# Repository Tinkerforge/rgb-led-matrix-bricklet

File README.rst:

RGB LED Matrix Bricklet
=======================

This repository contains the firmware source code and the hardware design
files. The documentation generator configs can be found at
https://github.com/Tinkerforge/generators

Repository Content
------------------

software/:
 * examples/: Examples for all supported languages
 * build/: Compiled files
 * src/: Source code of firmware
 * Makefile: Makefile to build project

hardware/:
 * Contains KiCad project files and additionally schematics as PDF

datasheets/:
 * Contains datasheets for sensors and complex ICs that are used

Hardware
--------

The hardware is designed with the open source EDA Suite KiCad
(http://www.kicad.org). Before you are able to open the files,
you have to install the Tinkerforge kicad-libraries
(https://github.com/Tinkerforge/kicad-libraries). You can either clone
them directly in hardware/ or clone them in a separate folder and
symlink them into hardware/
(ln -s kicad_path/kicad-libraries project_path/hardware). After that you
can open the .pro file in hardware/ with KiCad and from there view and
modify the schematics and the PCB layout.

Software
--------

If you want to do your own Brick/Bricklet firmware development we highly
recommend that you use our build environment setup script and read the
tutorial (https://www.tinkerforge.com/en/doc/Tutorials/Tutorial_Build_Environment/Tutorial.html).

To compile the C code we recommend you to install the newest GNU Arm Embedded
Toolchain (https://launchpad.net/gcc-arm-embedded/+download).
You also need to install bricklib2 (https://github.com/Tinkerforge/bricklib2).

You can either clone it directly in software/src/ or clone it in a
separate folder and symlink it into software/src/
(ln -s bricklib_path/bricklib2 project_path/software/src/). Finally make sure to
have CMake installed (http://www.cmake.org/cmake/resources/software.html).

After that you can build the firmware by invoking make in software/.
The firmware (.zbin) can then be found in software/build/ and uploaded
with brickv (click button "Flashing" on start screen).

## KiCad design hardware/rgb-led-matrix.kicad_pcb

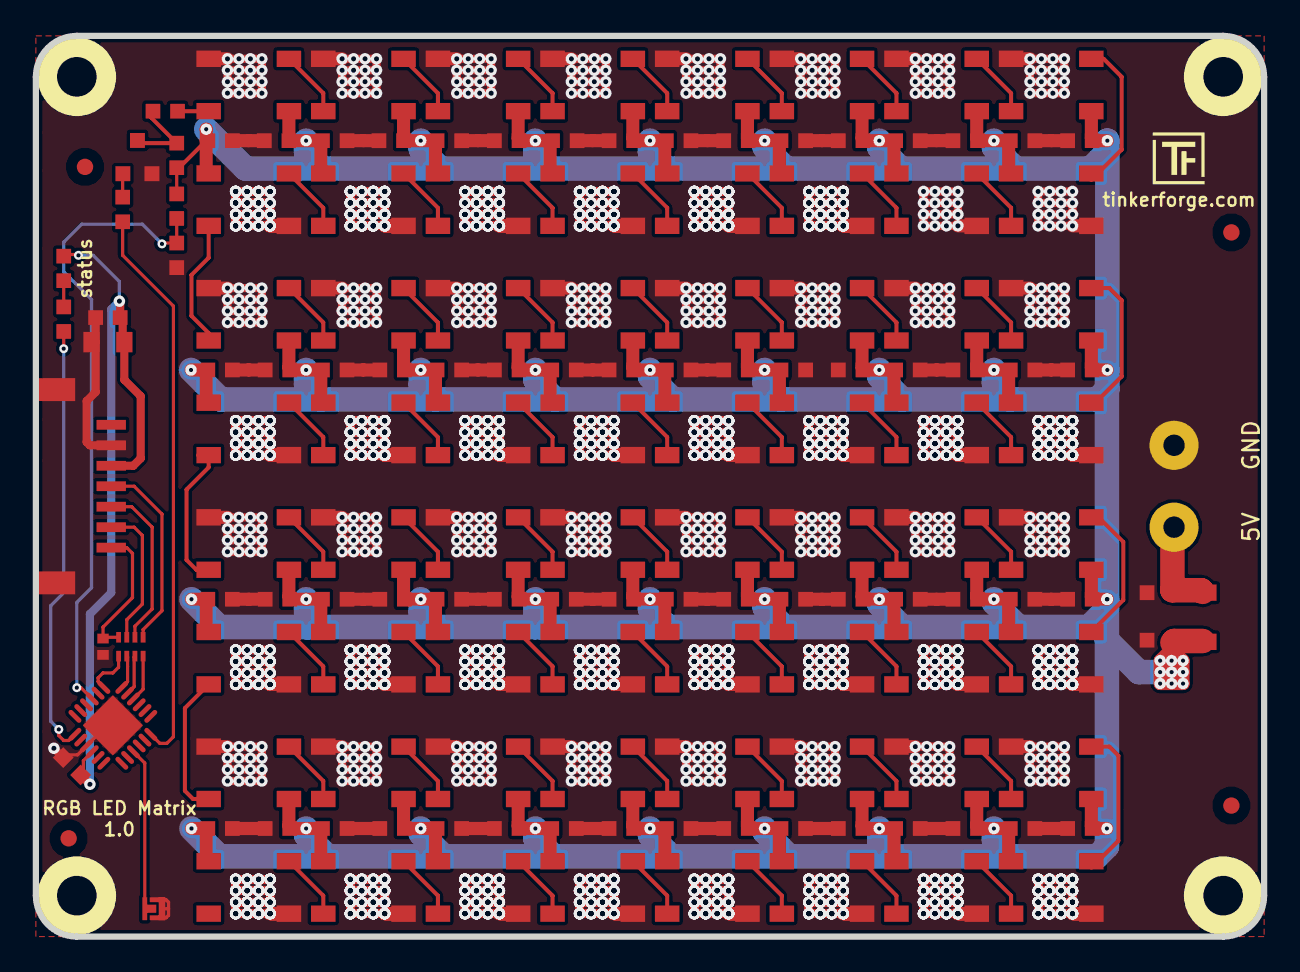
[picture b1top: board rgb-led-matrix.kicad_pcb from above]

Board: 2 copper layers, 75.0 x 55.0 mm, 157 parts (0 on the bottom side), 82 nets.

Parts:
C1, C6, C7, C8, C9, C10, C11, C12, C13, C14, C15, C16, C17, C18, C19, C20, C21, C22, C23, C24, C25, C26, C27, C28, C29, C30, C31, C32, C33, C34, C35, C36, C37, C38, C39, C40, C41, C42, C43, C44, C45, C46, C47, C48, C49, C50, C51, C52, C53, C54, C55, C56, C57, C58, C59, C60, C61, C62, C63, C64, C65, C66, C67, C68, C69: 100nF; C0603F
C2, C4, C5: 1uF; C0603F
C3: 10uF; C0805
C70: 220pF; C0402F
D1: LED blue; D0603F
FB2: FB 6A; R1206
Fiducial_Mark: VAL**; Fiducial_Mark
Fiducial_Mark#2, Fiducial_Mark#3, Fiducial_Mark#4: VAL**; Fiducial_Mark
J1: AKL_5_2
LED1, LED2, LED3, LED4, LED5, LED6, LED7, LED8, LED9, LED10, LED11, LED12, LED13, LED14, LED15, LED16, LED17, LED18, LED19, LED20, LED21, LED22, LED23, LED24, LED25, LED26, LED27, LED28, LED29, LED30, LED31, LED32, LED33, LED34, LED35, LED36, LED37, LED38, LED39, LED40, LED41, LED42, LED43, LED44, LED45, LED46, LED47, LED48, LED49, LED50, LED51, LED52, LED53, LED54, LED55, LED56, LED57, LED58, LED59, LED60, LED61, LED62, LED63, LED64: WS2812B_LED
P1: CONN_01X02; SolderJumper
P2: CON-SENSOR; CON-SENSOR2
Q1: 2N7002P; SOT23GDS
R1, R2, R5, R6: 1k; R0603F
R3: 100; R0603F
R4: 330; R0603F
RP1: 82; 4X0402
U1: XMC1100-16; QFN24-4x4mm-0.5mm
U2, U3, U4, U5: DRILL; DRILL_NP
VAL: CE_5mm

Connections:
3V3: C1.2, C2.2, C3.2, D1.1, P2.3, U1.10
GND: C1.1, C2.1, C3.1, C4.1, C5.1, C6.2, C7.2, C8.2, C9.2, C10.2, C11.2, C12.2, C13.2, C14.2, C15.2, C16.2, C17.2, C18.2, C19.2, C20.2, C21.2, C22.2, C23.2, C24.2, C25.2, C26.2, C27.2, C28.2, C29.2, C30.2, C31.2, C32.2, C33.2, C34.2, C35.2, C36.2, C37.2, C38.2, C39.2, C40.2, C41.2, C42.2, C43.2, C44.2, C45.2, C46.2, C47.2, C48.2, C49.2, C50.2, C51.2, C52.2, C53.2, C54.2, C55.2, C56.2, C57.2, C58.2, C59.2, C60.2, C61.2, C62.2, C63.2, C64.2, C65.2, C66.2, C67.2, C68.2, C69.2, C70.1, J1.1, LED1.3, LED2.3, LED3.3, LED4.3, LED5.3, LED6.3, LED7.3, LED8.3, LED9.3, LED10.3, LED11.3, LED12.3, LED13.3, LED14.3, LED15.3, LED16.3, LED17.3, LED18.3, LED19.3, LED20.3, LED21.3, LED22.3, LED23.3, LED24.3, LED25.3, LED26.3, LED27.3, LED28.3, LED29.3, LED30.3, LED31.3, LED32.3, LED33.3, LED34.3, LED35.3, LED36.3, LED37.3, LED38.3, LED39.3, LED40.3, LED41.3, LED42.3, LED43.3, LED44.3, LED45.3, LED46.3, LED47.3, LED48.3, LED49.3, LED50.3, LED51.3, LED52.3, LED53.3, LED54.3, LED55.3, LED56.3, LED57.3, LED58.3, LED59.3, LED60.3, LED61.3, LED62.3, LED63.3, LED64.3, P1.1, P2.2, P2.EP, Q1.S, R6.2, U1.9, U1.EXP
unnamed: C5.2, FB2.1, J1.2
unnamed: C70.2, P2.7, RP1.4
unnamed: D1.2, R1.1
unnamed: LED1.2, LED2.4
unnamed: LED1.4, R4.1
unnamed: LED2.2, LED3.4
unnamed: LED3.2, LED4.4
unnamed: LED4.2, LED5.4
unnamed: LED5.2, LED6.4
unnamed: LED6.2, LED7.4
unnamed: LED7.2, LED8.4
unnamed: LED8.2, LED9.4
unnamed: LED10.2, LED11.4
unnamed: LED9.2, LED10.4
unnamed: LED11.2, LED12.4
unnamed: LED12.2, LED13.4
unnamed: LED13.2, LED14.4
unnamed: LED14.2, LED15.4
unnamed: LED15.2, LED16.4
unnamed: LED16.2, LED17.4
unnamed: LED17.2, LED18.4
unnamed: LED18.2, LED19.4
unnamed: LED19.2, LED20.4
unnamed: LED20.2, LED21.4
unnamed: LED21.2, LED22.4
unnamed: LED22.2, LED23.4
unnamed: LED23.2, LED24.4
unnamed: LED24.2, LED25.4
unnamed: LED25.2, LED26.4
unnamed: LED26.2, LED27.4
unnamed: LED27.2, LED28.4
unnamed: LED28.2, LED29.4
unnamed: LED29.2, LED30.4
unnamed: LED30.2, LED31.4
unnamed: LED31.2, LED32.4
unnamed: LED32.2, LED33.4
unnamed: LED33.2, LED34.4
unnamed: LED34.2, LED35.4
unnamed: LED35.2, LED36.4
unnamed: LED36.2, LED37.4
unnamed: LED37.2, LED38.4
unnamed: LED38.2, LED39.4
unnamed: LED39.2, LED40.4
unnamed: LED40.2, LED41.4
unnamed: LED41.2, LED42.4
unnamed: LED42.2, LED43.4
unnamed: LED43.2, LED44.4
unnamed: LED44.2, LED45.4
unnamed: LED45.2, LED46.4
unnamed: LED46.2, LED47.4
unnamed: LED47.2, LED48.4
unnamed: LED48.2, LED49.4
unnamed: LED49.2, LED50.4
unnamed: LED50.2, LED51.4
unnamed: LED51.2, LED52.4
unnamed: LED52.2, LED53.4
unnamed: LED53.2, LED54.4
unnamed: LED54.2, LED55.4
unnamed: LED55.2, LED56.4
unnamed: LED56.2, LED57.4
unnamed: LED57.2, LED58.4
unnamed: LED58.2, LED59.4
unnamed: LED59.2, LED60.4
unnamed: LED60.2, LED61.4
unnamed: LED61.2, LED62.4
unnamed: LED62.2, LED63.4
unnamed: LED63.2, LED64.4
unnamed: P1.2, U1.15
unnamed: P2.4, RP1.1
unnamed: P2.5, RP1.2
unnamed: P2.6, RP1.3
unnamed: R1.2, U1.7
unnamed: R2.1, R4.2
unnamed: R3.2, U1.18
S-CLK: RP1.7, U1.23
S-CS: RP1.8, U1.22
S-MISO: RP1.5, U1.1
S-MOSI: RP1.6, U1.24
VCC: C4.2, C6.1, C7.1, C8.1, C9.1, C10.1, C11.1, C12.1, C13.1, C14.1, C15.1, C16.1, C17.1, C18.1, C19.1, C20.1, C21.1, C22.1, C23.1, C24.1, C25.1, C26.1, C27.1, C28.1, C29.1, C30.1, C31.1, C32.1, C33.1, C34.1, C35.1, C36.1, C37.1, C38.1, C39.1, C40.1, C41.1, C42.1, C43.1, C44.1, C45.1, C46.1, C47.1, C48.1, C49.1, C50.1, C51.1, C52.1, C53.1, C54.1, C55.1, C56.1, C57.1, C58.1, C59.1, C60.1, C61.1, C62.1, C63.1, C64.1, C65.1, C66.1, C67.1, C68.1, C69.1, FB2.2, LED1.1, LED2.1, LED3.1, LED4.1, LED5.1, LED6.1, LED7.1, LED8.1, LED9.1, LED10.1, LED11.1, LED12.1, LED13.1, LED14.1, LED15.1, LED16.1, LED17.1, LED18.1, LED19.1, LED20.1, LED21.1, LED22.1, LED23.1, LED24.1, LED25.1, LED26.1, LED27.1, LED28.1, LED29.1, LED30.1, LED31.1, LED32.1, LED33.1, LED34.1, LED35.1, LED36.1, LED37.1, LED38.1, LED39.1, LED40.1, LED41.1, LED42.1, LED43.1, LED44.1, LED45.1, LED46.1, LED47.1, LED48.1, LED49.1, LED50.1, LED51.1, LED52.1, LED53.1, LED54.1, LED55.1, LED56.1, LED57.1, LED58.1, LED59.1, LED60.1, LED61.1, LED62.1, LED63.1, LED64.1, R2.2, R5.1
VIN: R5.2, R6.1, U1.3

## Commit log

2015-11-18 hardware files copied from rgb led bricklet
2015-11-18 leds not fully placed and routed
2015-11-23 fully routed
2015-12-30 todo add voltage measurement
2016-02-09 Add WIP marker
2017-02-06 Add auto-generated firmware stub
2017-02-06 Implement API
2017-02-06 Add stub for matrix driver
2017-02-06 Add matrix driver config
2017-02-06 Add WS2812 datasheet
2017-02-06 Add missing string.h (for memcpy)
2017-02-06 Use rgb struct for in buffer and single array for out buffer
2017-02-06 Implement SPI communication and byte stuffing (untested)
2017-02-06 Make for-loop more efficient
2017-02-06 Use 6.4MHz SPI frequency
2017-02-07 add xmc1100 microcontroller
2017-02-07 add vias for better cooling
2017-02-07 fix license date
2017-02-08 add fiducials and logos
2017-02-08 remove old text
2017-03-07 Set correct pins, versions and sizes
2017-03-07 Remove debug
2017-03-07 Add voltage measurement support
2017-03-07 Use correct polarity and timing for SPI
2017-03-07 Disable debug
2017-03-07 Add vadc support to makefile
2017-03-07 Add voltage input channel define
2017-03-07 Increase adc sample time to maximum
2017-03-09 Use GRB as correct color sequence for WS2812B
2017-03-09 Don't use HWCTRL
2017-03-09 Use full 32 byte buffer and trigger interrupt if 4 bytes have been used
2017-03-09 Decrease frequency by sending 2 bits per byte
2017-03-09 Use 4 bits per bit instead of 8
2017-03-09 Increase interrupt speed by using pointer instead of indexes, incrementing frame number later on and putting buffer end check at end of loop
2017-03-09 sort pixels so they appear left to right and top to bottom
2017-03-13 Use 16 bits per word to save 50% time during interrupt
2017-04-12 Add rx/tx information to allow for hald-fuplex bootstrapper flashing
2017-05-08 fix spi filtering
2017-05-12 Fix CE logo
2017-05-18 fix led connection
2017-05-18 adapt led pin accoring to hardware
2017-05-18 define ferrite
2017-06-09 Put interrupt in ram for faster function call
2017-06-09 make sure element 0 is initialized correctly
2017-08-01 Add 3d information (fam)
2017-08-01 Add 3d model (*.step & *.FCStd)
2017-08-10 Add WS2812B datasheet
2017-08-11 specify filter circuit
2017-09-08 add status led description text
2017-09-19 specify processor
2017-11-06 Add final schematic
2017-11-06 Rename
2017-11-09 Make sure draf frame function (with frame duration = 0) works properly
2017-11-21 Remove WIP marker
2017-11-23 Remove power connector
2018-02-20 Cleanup KiCad libraries config
    Ensure LibDir=kicad-libraries and LibName1=tinkerforge.
    Remove special library.
2018-03-05 Remove unused flash-size define
2018-06-18 Change capacitor footprint(s) to C0402F
2018-06-28 Fix readme
2018-07-11 Add Makefile with docker support
2018-07-11 Update directory structure and build instructions
2018-07-11 Remove obsolete generate_makefile scripts
2018-10-04 Increase version for new release (changes in bricklib2)
2018-10-04 Add rev to changelog
2018-11-06 Adapt struct names to common naming convention
2019-02-04 repair schematic
2021-10-25 Update KiCad link
    https://www.kicad.org/blog/2021/10/Avoid-links-to-former-kicad-domain/
2022-07-06 Add license files.
2025-10-04 Fix compatibility with new Docker build image (GCC 14.2.1)

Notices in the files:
hardware/rgb-led-matrix.kicad_pcb:
Licensed under CERN OHL v.1.1
Copyright (©) 2017, B.Nordmeyer
Copyright Tinkerforge GmbH 2017.
This documentation describes Open Hardware and is licensed under the
CERN OHL v. 1.1.
